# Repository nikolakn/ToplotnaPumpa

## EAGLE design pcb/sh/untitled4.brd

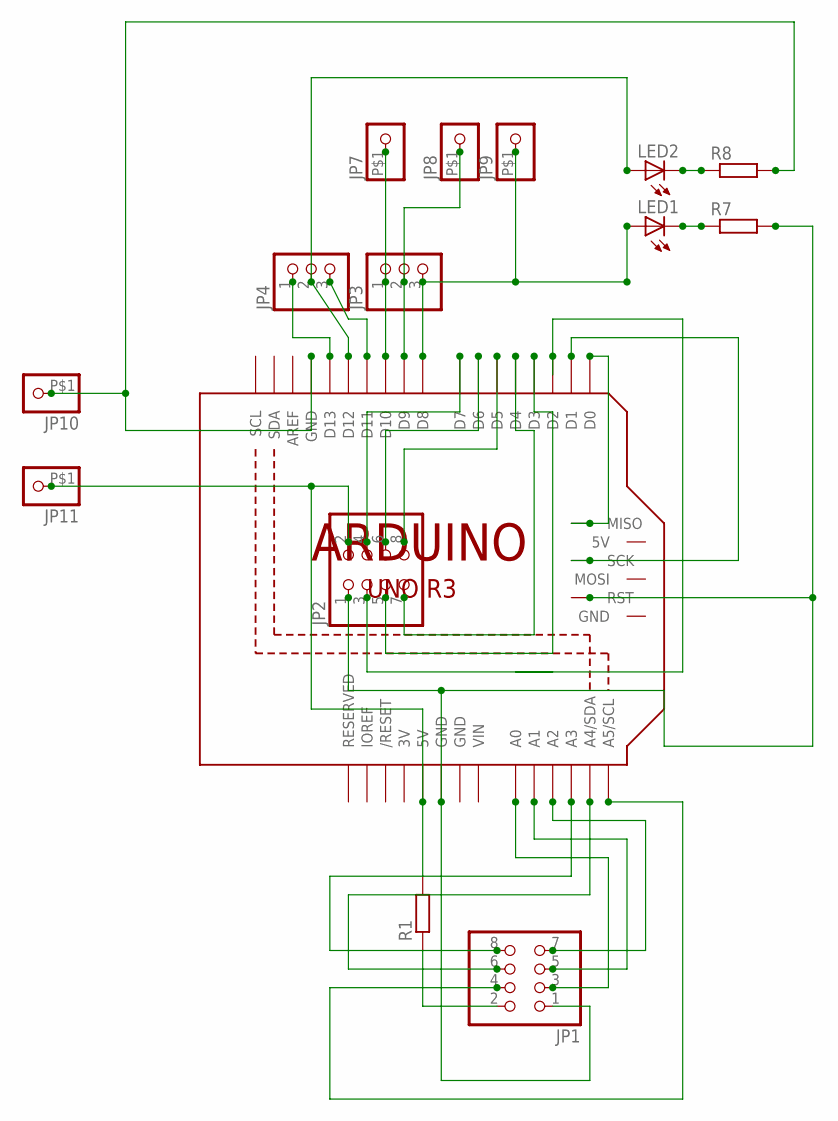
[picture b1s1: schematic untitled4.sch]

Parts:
JP1, JP2: PINHD-2X4; 2X04
JP3, JP4: PINHD-1X3; 1X03
JP7, JP8, JP9, JP10, JP11: PINHD-1X1-BIGPOGO; 1X1-BIGPOGO
LED1, LED2: LED3MM
M1: ARDUINO_R3_ICSP_NODIM; ARDUINOR3_ICSP_NODIM
R1, R7, R8: R-EU_0207/10; 0207/10

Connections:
3V: M1.3V
GND: M1.GND@3 (GND)
unnamed: JP2.2, JP11.P$1, M1.5V, R1.2
unnamed: M1.D0, M1.MISO
unnamed: M1.D1, M1.SCK
unnamed: JP1.2, R1.1
unnamed: JP1.3, M1.A0
unnamed: JP1.5, M1.A1
unnamed: JP1.7, M1.A2
unnamed: JP2.5, M1.D3
unnamed: JP2.3, M1.D2
unnamed: JP2.6, M1.D6
unnamed: JP2.4, M1.D7
unnamed: JP2.8, M1.D5
unnamed: JP2.7, M1.D4
unnamed: JP1.8, M1.A3
unnamed: JP1.6, M1.A4 (A4/SDA)
unnamed: LED1.K (C), R7.1
unnamed: JP4.3, M1.D11
unnamed: JP10.P$1, M1.GND, R8.2
unnamed: JP1.4, M1.A5 (A5/SCL)
unnamed: LED2.K (C), R8.1
unnamed: JP4.2, LED2.A, M1.D12
unnamed: JP4.1, M1.D13
unnamed: JP3.2, JP8.P$1, M1.D9
unnamed: JP3.1, JP7.P$1, M1.D10
unnamed: JP3.3, JP9.P$1, LED1.A, M1.D8
unnamed: JP1.1, JP2.1, M1.GND@1 (GND), R7.2
VIN: M1.VIN

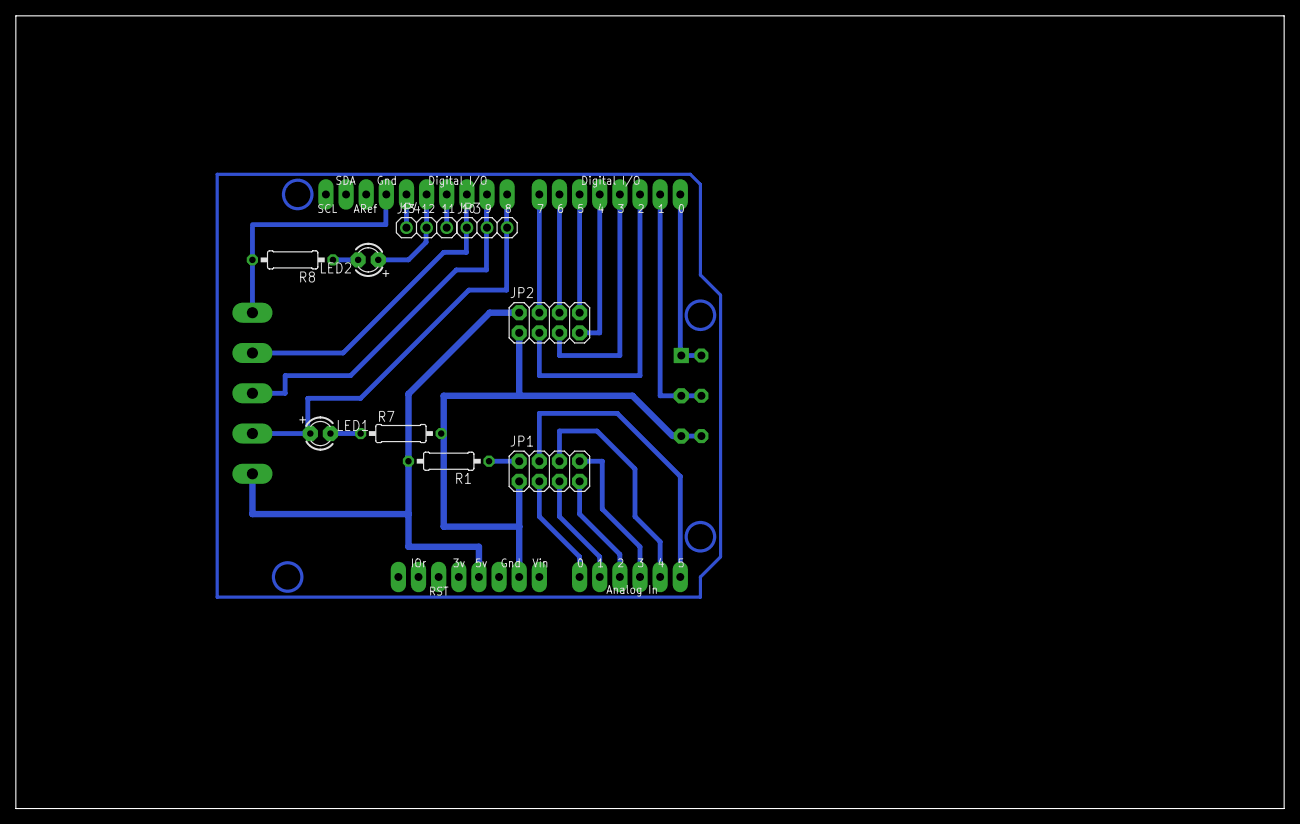
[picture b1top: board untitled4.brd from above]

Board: 2 copper layers, 160.0 x 100.0 mm, 15 parts (0 on the bottom side), 26 nets.

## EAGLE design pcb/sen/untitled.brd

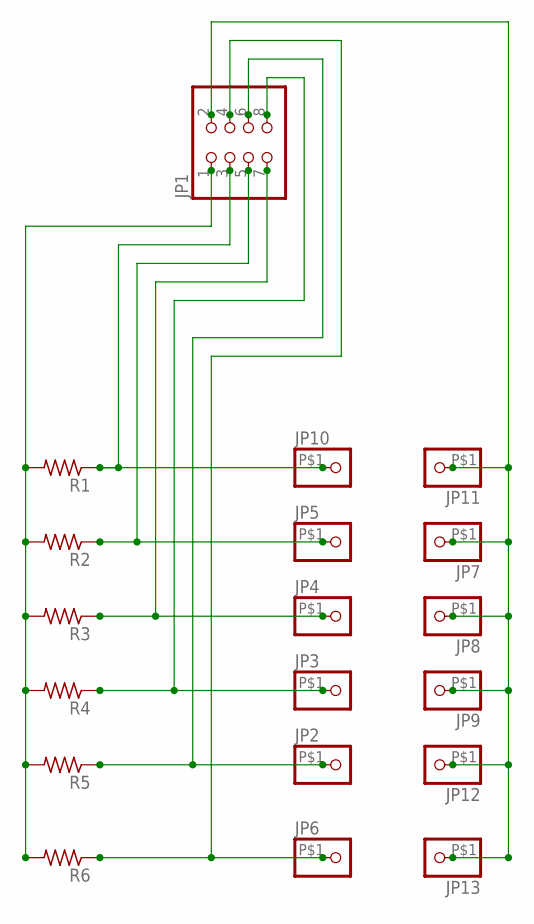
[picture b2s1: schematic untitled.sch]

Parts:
JP1: PINHD-2X4; 2X04
JP2, JP3, JP4, JP5, JP6, JP7, JP8, JP9, JP10, JP11, JP12, JP13: PINHD-1X1-BIGPOGO; 1X1-BIGPOGO
R1, R2, R3, R4, R5, R6: R-US_0204/7; 0204/7

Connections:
unnamed: JP1.1, R1.2, R2.2, R3.2, R4.2, R5.2, R6.2
unnamed: JP1.3, JP10.P$1, R1.1
unnamed: JP1.2, JP7.P$1, JP8.P$1, JP9.P$1, JP11.P$1, JP12.P$1, JP13.P$1
unnamed: JP1.5, JP5.P$1, R2.1
unnamed: JP1.7, JP4.P$1, R3.1
unnamed: JP1.8, JP3.P$1, R4.1
unnamed: JP1.6, JP2.P$1, R5.1
unnamed: JP1.4, JP6.P$1, R6.1

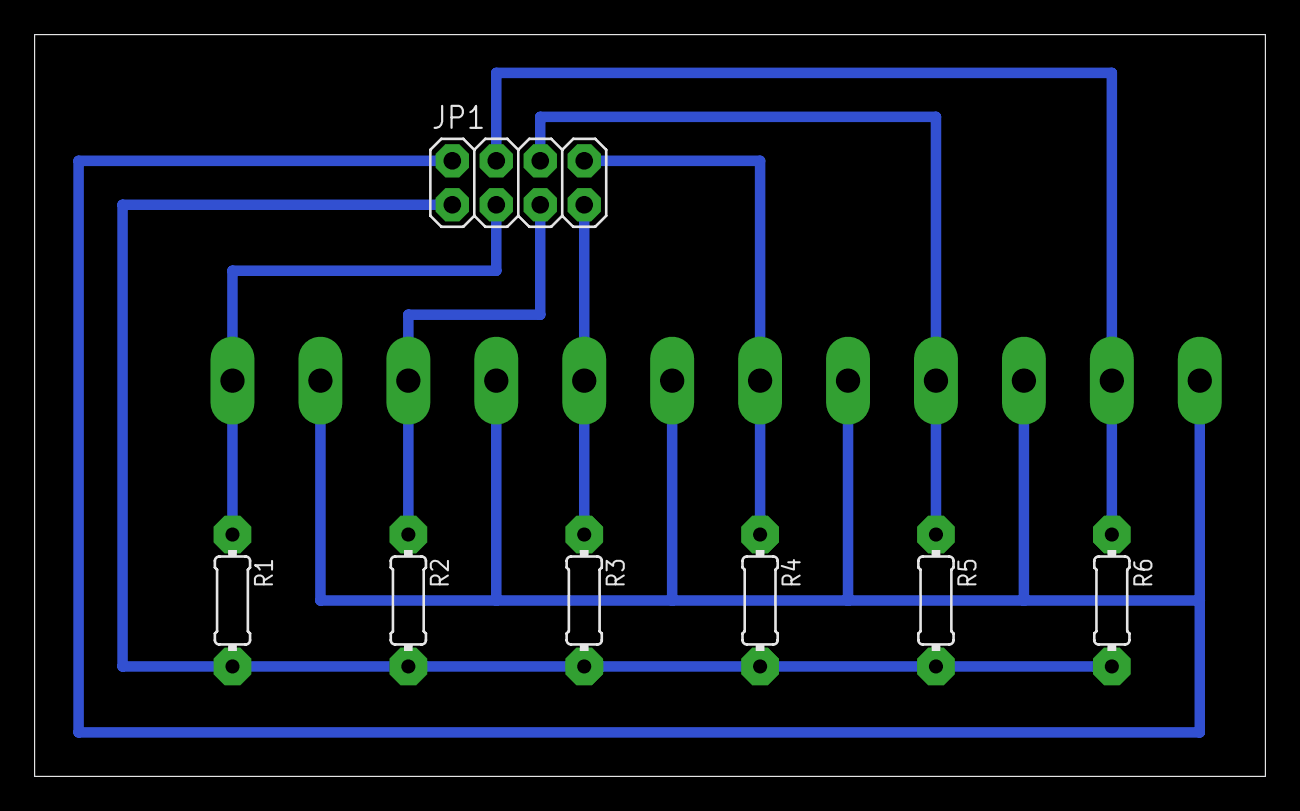
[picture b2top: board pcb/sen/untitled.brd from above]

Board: 2 copper layers, 71.1 x 42.8 mm, 19 parts (0 on the bottom side), 8 nets.

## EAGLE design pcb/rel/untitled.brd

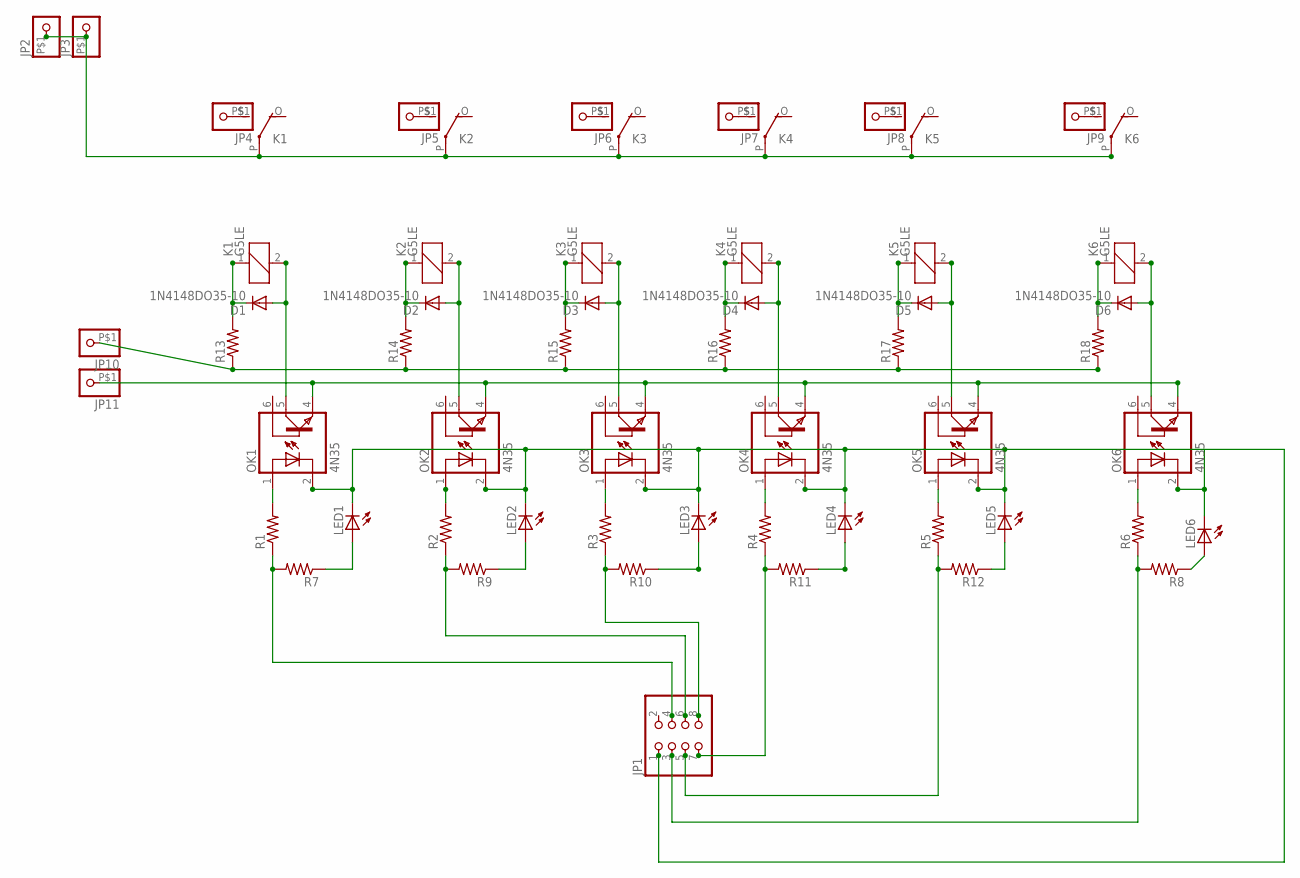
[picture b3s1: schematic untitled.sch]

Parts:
D1, D2, D3, D4, D5, D6: 1N4148DO35-10; DO35-10
JP1: PINHD-2X4; 2X04
JP2, JP3, JP4, JP5, JP6, JP7, JP8, JP9, JP10, JP11: PINHD-1X1-BIGPOGO; 1X1-BIGPOGO
K1, K2, K3, K4, K5, K6: G5LE
LED1, LED2, LED3, LED4, LED5, LED6: LED3MM
OK1, OK2, OK3, OK4, OK5, OK6: 4N35; DIL06
R1, R2, R3, R4, R5, R6, R7, R8, R9, R10, R11, R12, R13, R14, R15, R16, R17, R18: R-US_0204/7; 0204/7

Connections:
unnamed: OK1.1 (A), R1.2
unnamed: OK2.1 (A), R2.2
unnamed: OK3.1 (A), R3.2
unnamed: OK4.1 (A), R4.2
unnamed: OK5.1 (A), R5.2
unnamed: JP1.4, R1.1, R7.2
unnamed: JP1.6, R2.1, R9.2
unnamed: JP1.8, R3.1, R10.2
unnamed: JP1.7, R4.1, R11.2
unnamed: JP1.5, R5.1, R12.2
unnamed: JP1.3, R6.1, R8.2
unnamed: JP1.1, LED1.K (C), LED2.K (C), LED3.K (C), LED4.K (C), LED5.K (C), LED6.K (C), OK1.2 (C), OK2.2 (C), OK3.2 (C), OK4.2 (C), OK5.2 (C), OK6.2 (C)
unnamed: OK6.1 (A), R6.2
unnamed: LED6.A, R8.1
unnamed: LED1.A, R7.1
unnamed: LED2.A, R9.1
unnamed: LED3.A, R10.1
unnamed: LED4.A, R11.1
unnamed: LED5.A, R12.1
unnamed: D6.A, K6.2, OK6.5 (COL)
unnamed: D5.A, K5.2, OK5.5 (COL)
unnamed: D4.A, K4.2, OK4.5 (COL)
unnamed: D3.A, K3.2, OK3.5 (COL)
unnamed: D2.A, K2.2, OK2.5 (COL)
unnamed: D1.A, K1.2, OK1.5 (COL)
unnamed: D1.C, K1.1, R13.2
unnamed: D2.C, K2.1, R14.2
unnamed: D3.C, K3.1, R15.2
unnamed: D4.C, K4.1, R16.2
unnamed: D5.C, K5.1, R17.2
unnamed: D6.C, K6.1, R18.2
unnamed: JP2.P$1, JP3.P$1, K1.P, K2.P, K3.P, K4.P, K5.P, K6.P
unnamed: JP4.P$1, K1.S
unnamed: JP10.P$1, R13.1, R14.1, R15.1, R16.1, R17.1, R18.1
unnamed: JP6.P$1, K3.S
unnamed: JP5.P$1, K2.S
unnamed: JP11.P$1, OK1.4 (EMI), OK2.4 (EMI), OK3.4 (EMI), OK4.4 (EMI), OK5.4 (EMI), OK6.4 (EMI)
unnamed: JP7.P$1, K4.S
unnamed: JP8.P$1, K5.S
unnamed: JP9.P$1, K6.S

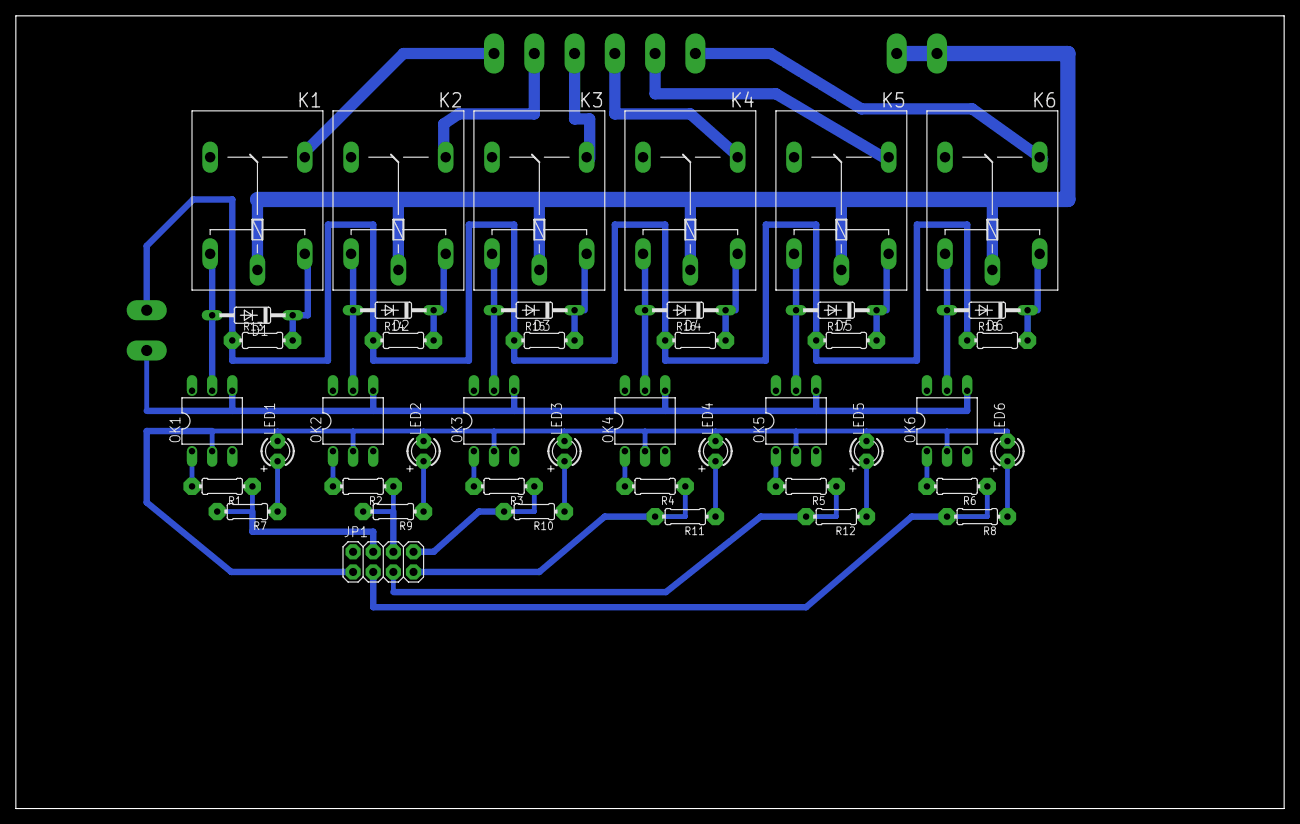
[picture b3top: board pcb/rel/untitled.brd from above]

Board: 2 copper layers, 160.0 x 100.0 mm, 53 parts (0 on the bottom side), 40 nets.

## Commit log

2015-11-06 init
